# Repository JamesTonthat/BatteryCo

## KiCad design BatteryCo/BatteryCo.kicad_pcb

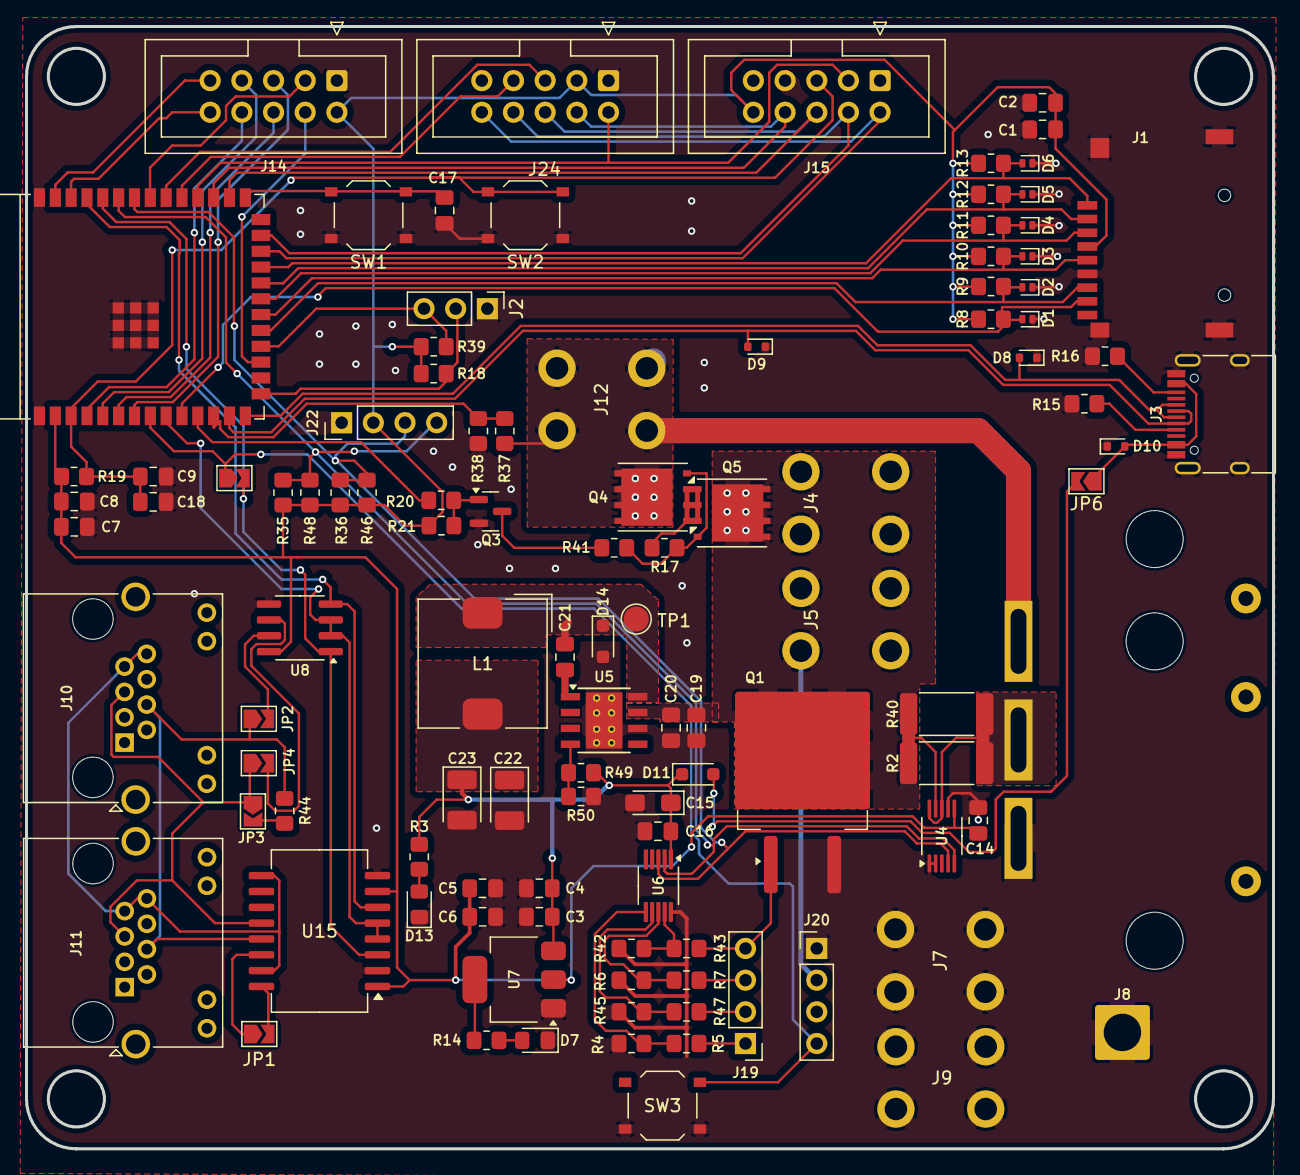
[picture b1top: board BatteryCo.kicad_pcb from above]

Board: 2 copper layers, 100.0 x 90.0 mm, 108 parts (0 on the bottom side), 70 nets.

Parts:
C1, C3, C6, C7, C19, C20: 10uF/25V(20%); C_0805_2012Metric_Pad1.18x1.45mm_HandSolder
C2, C4, C5, C8, C14, C16, C17, C18: 0.1uF/50V(10%); C_0805_2012Metric_Pad1.18x1.45mm_HandSolder
C9: 1uF/16V(10%); C_0805_2012Metric_Pad1.18x1.45mm_HandSolder
C15: 10uF/25V(20%); CP_EIA-3216-18_Kemet-A_Pad1.58x1.35mm_HandSolder
C21: 10nF/50V(10%); C_0805_2012Metric_Pad1.18x1.45mm_HandSolder
C22, C23: 33uF/10V(10%); CP_EIA-3528-21_Kemet-B_Pad1.50x2.35mm_HandSolder
D1, D2, D3, D4, D5, D6: LESD8D3.3CAT5G; D_SOD-882D
D7, D13: LED; LED_0805_2012Metric_Pad1.15x1.40mm_HandSolder
D8, D9, D10: LESD5D5.0CT1G; D_SOD-523
D11, D14: 1N5819WS; D_SOD-323_HandSoldering
J1: Micro_SD_Card_Det2; Hanbo TF-012D
J2: Conn_01x03; PinHeader_1x03_P2.54mm_Vertical
J3: USB_C_Receptacle_USB2.0_16P; USB_C_Receptacle_HRO_TYPE-C-31-M-12
J4, J5, J7, J9, J12: Conn_01x01; T44001
J8: Conn_01x01; SolderWire-2.5sqmm_1x01_D2.4mm_OD4.4mm
J10, J11: RJ45_LED_Shielded; RJ45_Amphenol_RJHSE538X
J14: Conn_02x05_Counter_Clockwise; IDC-Header_2x05_P2.54mm_Vertical
J15, J24: Conn_02x05_Odd_Even; IDC-Header_2x05_P2.54mm_Vertical
J16: Conn_01x03; 45A-ANGLE-PAIR
J19, J20: Conn_01x04; PinHeader_1x04_P2.54mm_Vertical
J22: I2C_BUS0; PinHeader_1x04_P2.54mm_Vertical
JP1, JP2, JP3, JP4, JP5, JP6: SolderJumper_2_Open; SolderJumper-2_P1.3mm_Open_TrianglePad1.0x1.5mm
L1: SLF10145T-101M1R0-PF; L_TDK_SLF10145
Q1: IRLZ44SPbF; TO-263-2
Q3: AO3400A; SOT-23
Q4, Q5: AON6411; AO_DFN-8-1EP_5.55x5.2mm_P1.27mm_EP4.12x4.6mm
R2, R40: 5m; R_2512_6332Metric_Pad1.40x3.35mm_HandSolder
R3: 47K (1%); R_0805_2012Metric_Pad1.20x1.40mm_HandSolder
R4, R6, R8, R9, R10, R11, R12, R13, R17, R18, R19, R21, R37, R39, R42, R45, R49: 10K (1%); R_0805_2012Metric_Pad1.20x1.40mm_HandSolder
R5, R7, R43, R47: 330 (1%); R_0805_2012Metric_Pad1.20x1.40mm_HandSolder
R14, R41: 5.1K (1%); R_0805_2012Metric_Pad1.20x1.40mm_HandSolder
R15, R16, R35, R36, R46, R48: 4.7K (1%); R_0805_2012Metric_Pad1.20x1.40mm_HandSolder
R20: 100 (1%); R_0805_2012Metric_Pad1.20x1.40mm_HandSolder
R38: 1.5k (1%); R_0805_2012Metric_Pad1.20x1.40mm_HandSolder
R44: 120 (1%); R_0805_2012Metric_Pad1.20x1.40mm_HandSolder
R50: 3.3K (1%); R_0805_2012Metric_Pad1.20x1.40mm_HandSolder
SW1, SW2, SW3: SW_Push; SW_Push_1P1T_XKB_TS-1187A
TP1: TestPoint; TestPoint_Pad_D2.0mm
U1: ESP32-S3-WROOM-1
U4: INA228; VSSOP-10_3x3mm_P0.5mm
U5: TPS5430DDA; TI_SO-PowerPAD-8_ThermalVias
U6: MCP4728; MSOP-10_3x3mm_P0.5mm
U7: AMS1117-3.3; SOT-223-3_TabPin2
U8: SP3485EN; SOIC-8_3.9x4.9mm_P1.27mm
U15: CA-IS13092VW; SOIC-16W_7.5x12.8mm_P1.27mm

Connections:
+5V: C3.1, C4.1, C15.1, C16.1, C22.1, C23.1, D11.1 (K), L1.2, R3.1, R49.1, U6.1 (VDD), U7.3 (VI)
BIT_0: J14.10, U1.38 (GPIO2/TOUCH2/ADC1_CH1)
BIT_1: J14.9, U1.39 (GPIO1/TOUCH1/ADC1_CH0)
BIT_2: J14.8, U1.4 (GPIO4/TOUCH4/ADC1_CH3)
BIT_3: J14.7, U1.5 (GPIO5/TOUCH5/ADC1_CH4)
BIT_4: J14.6, U1.6 (GPIO6/TOUCH6/ADC1_CH5)
BIT_5: J14.5, U1.7 (GPIO7/TOUCH7/ADC1_CH6)
BIT_6: J14.4, U1.17 (GPIO9/TOUCH9/ADC1_CH8/FSPIHD/SUBSPIHD)
CHARGER_OFF: R20.2, U1.11 (GPIO18/U1RXD/ADC2_CH7/CLK_OUT3)
CHIP_PU: C9.1, C18.2, J15.5, R19.1, SW2.1, U1.3 (EN)
D1: C21.2, D14.1 (K), L1.1, TP1.1, U5.8 (PH)
ESP_3V3: C1.1, C2.1, C5.1, C6.1, C7.1, C8.1, C14.1, J1.4 (VDD), J14.2, J15.10, J22.2, J24.3, R8.2, R9.2, R10.2, R11.2, R12.2, R13.2, R14.1, R18.1, R19.2, R21.1, R35.1, R36.1, R39.1, R46.1, R48.1, U1.2 (3V3), U4.6 (VS), U7.2 (VO), U8.8 (VCC), U15.1 (VCC), U15.7 (VCCL)
FAN_PWM: J20.4, JP5.1 (A), SW3.2, U1.8 (GPIO15/U0RTS/ADC2_CH4/XTAL_32K_P)
GND3: J10.7, J10.8, J11.7, J11.8, U15.9 (GNDB), U15.15 (GNDB)
GPIO0: C17.2, SW1.2, U1.27 (GPIO0/BOOT)
GPIO19: D9.2 (A2), J3.A7 (D-), J3.B7 (D-), U1.13 (GPIO19/U1RTS/ADC2_CH8/CLK_OUT2/USB_D-)
GPIO20: D8.2 (A2), J3.A6 (D+), J3.B6 (D+), U1.14 (GPIO20/U1CTS/ADC2_CH9/CLK_OUT1/USB_D+)
LCD_SCL: J24.5, U1.32 (MTCK/GPIO39/CLK_OUT3/SUBSPICS1)
LCD_SDA: J24.7, U1.31 (GPIO38/FSPIWP/SUBSPIWP)
LED_ON: J14.3, U1.33 (MTDO/GPIO40/CLK_OUT2)
unnamed: D7.2 (A), R14.2
unnamed: D11.2 (A), JP6.2 (B)
unnamed: D13.2 (A), R3.2
unnamed: J3.A5 (CC1), R15.2
unnamed: J3.B5 (CC2), R16.2
unnamed: JP1.1 (A), U15.14 (VISOIN)
unnamed: JP1.2 (B), U15.16 (VISOOUT)
unnamed: J10.4, J11.4, JP2.1 (A), R44.1, U15.13 (B)
unnamed: JP2.2 (B), U8.7 (B)
unnamed: J10.5, J11.5, JP3.1 (A), JP4.1 (A), U15.12 (A)
unnamed: JP3.2 (B), R44.2
unnamed: JP4.2 (B), U8.6 (A)
unnamed: Q3.3 (D), R41.2
unnamed: Q3.1 (G), R20.1, R21.2
unnamed: Q4.4 (G), Q5.4 (G), R17.2, R41.1
unnamed: Q4.1 (S), Q4.2 (S), Q4.3 (S), Q5.1 (S), Q5.2 (S), Q5.3 (S), R17.1
unnamed: C21.1, U5.1 (BOOT)
unnamed: R49.2, R50.1, U5.4 (VSENSE)
PHOTO_1: J2.2, R18.2, U1.15 (GPIO3/TOUCH3/ADC1_CH2)
PHOTO_2: J2.3, R39.2, U1.18 (GPIO10/TOUCH10/ADC1_CH9/FSPICS0/FSPIIO4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)
RE: U1.9 (GPIO16/U0CTS/ADC2_CH5/XTAL_32K_N), U8.2 (~RE), U8.3 (DE), U15.4 (~RE), U15.5 (DE)
SCL: J22.4, R35.2, R48.2, U1.35 (MTMS/GPIO42), U4.5 (SCL), U6.2 (SCL)
SDA: J22.3, R36.2, R46.2, U1.34 (MTDI/GPIO41/CLK_OUT1), U4.4 (SDA), U6.3 (SDA)
SD_CLK: D3.2 (A2), J1.5 (CLK), R10.1, U1.20 (GPIO12/TOUCH12/ADC2_CH1/FSPICLK/FSPIIO6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)
SD_CMD: D4.2 (A2), J1.3 (CMD), R11.1, U1.21 (GPIO13/TOUCH13/ADC2_CH2/FSPIQ/FSPIIO7/S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)
SD_DATA0: D2.2 (A2), J1.7 (DAT0), R9.1, U1.19 (GPIO11/TOUCH11/ADC2_CH0/FSPID/FSPIIO5/S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)
SD_DATA1: D1.2 (A2), J1.8 (DAT1), R8.1, U1.10 (GPIO17/U1TXD/ADC2_CH6)
SD_DATA2: D6.2 (A2), J1.1 (DAT2), R13.1, U1.23 (GPIO21)
SD_DATA3: D5.2 (A2), J1.2 (DAT3/CD), R12.1, U1.22 (GPIO14/TOUCH14/ADC2_CH3/FSPIWP/FSPIDQS/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)
U0RXD: JP5.2 (B), U1.36 (U0RXD/GPIO44/CLK_OUT2), U8.1 (RO), U15.3 (RO)
U0TXD: U1.37 (U0TXD/GPIO43/CLK_OUT1), U8.4 (DI), U15.6 (DI)
VBUSB: D10.2 (A2), J3.A4 (VBUS), J3.A9 (VBUS), J3.B4 (VBUS), J3.B9 (VBUS), JP6.1 (A)
V_BATT+: J16.2, R2.2, R40.2, U4.8 (Vbus), U4.10 (Vin+)
V_BATT-: C1.2, C2.2, C3.2, C4.2, C5.2, C6.2, C7.2, C8.2, C9.2, C14.2, C15.2, C16.2, C17.1, C18.1, C19.2, C20.2, C22.2, C23.2, D1.1 (A1), D2.1 (A1), D3.1 (A1), D4.1 (A1), D5.1 (A1), D6.1 (A1), D7.1 (K), D8.1 (A1), D9.1 (A1), D10.1 (A1), D13.1 (K), D14.2 (A), J1.6 (VSS), J1.10 (SHIELD), J2.1, J3.A1 (GND), J3.A12 (GND), J3.B1 (GND), J3.B12 (GND), J3.S1 (SHIELD), J7.1, J8.1, J9.1, J14.1, J15.7, J16.3, J20.1, J22.1, J24.1, Q1.3 (S), Q3.2 (S), R4.2, R6.2, R15.1, R16.1, R38.2, R42.2, R45.2, R50.2, SW1.1, SW2.2, SW3.1, U1.1 (GND), U1.40 (GND), U1.41 (GND), U4.1 (A1), U4.2 (A0), U4.7 (GND), U5.6 (GND), U5.9 (GNDPAD), U6.10 (VSS), U7.1 (GND), U8.5 (GND), U15.2 (GNDA), U15.8 (GNDA)
V_CHA: R4.1, R5.1, U6.6 (VOUTA)
V_CHARGER+: J12.1, J16.1, Q4.5 (D), R37.1
V_CHARGER_REF: R37.2, R38.1, U1.12 (GPIO8/TOUCH8/ADC1_CH7/SUBSPICS1)
V_CHA_OUT: J19.1, R5.2
V_CHB: R45.1, R47.1, U6.7 (VOUTB)
V_CHB_OUT: J19.2, R47.2
V_CHC: R6.1, R7.1, U6.8 (VOUTC)
V_CHC_OUT: J19.3, R7.2
V_CHD: R42.1, R43.1, U6.9 (VOUTD)
V_CHD_OUT: J19.4, Q1.1 (G), R43.2
V_LOAD+: C19.1, C20.1, J4.1, J5.1, J20.2, Q1.2 (D), Q5.5 (D), R2.1, R40.1, U4.9 (Vin-), U5.7 (VIN)
W_INT: J15.3, J24.2, U1.30 (SPIDQS/GPIO37/FSPIQ/SUBSPIQ)
W_MISO: J15.8, J24.4, U1.29 (SPIIO7/GPIO36/FSPICLK/SUBSPICLK)
W_MOSI: J15.6, J24.6, U1.28 (SPIIO6/GPIO35/FSPID/SUBSPID)
W_SCLK: J15.2, J24.10, U1.24 (GPIO47/SPICLK_P/SUBSPICLK_P_DIFF)
W_SCS: J15.4, J24.8, U1.25 (GPIO48/SPICLK_N/SUBSPICLK_N_DIFF)

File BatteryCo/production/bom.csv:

Designator,Footprint,Quantity,Value,LCSC Part #
"C1, C12, C13, C3, C6, C7",0805,6,10uF/25V(20%),C15850
"C10, C11, C14, C16, C17, C18, C2, C4, C5, C8",0805,10,0.1uF/50V(10%),C49678
C15,CP_EIA-3216-18_Kemet-A_Pad1.58x1.35mm_HandSolder,1,10uF/25V(20%),C7171
C9,0805,1,1uF/16V(10%),C28323
"D1, D2, D3, D4, D5, D6",D_SOD-882D,6,LESD8D3.3CAT5G,C5199186
"D10, D8, D9",D_SOD-523,3,LESD5D5.0CT1G,C383211
D11,D_SOD-323,1,1N5819WS,C191023
D13,0805,1,LED,C2297
D7,0805,1,LED,C84256
J1,Hanbo TF-012D,1,Micro_SD_Card_Det2,C2874207
"J12, J13, J16, J17, J18, J4, J5, J6, J7, J8, J9",SolderWire-2.5sqmm_1x01_D2.4mm_OD4.4mm,11,Conn_01x01,
J3,USB_C_Receptacle_HRO_TYPE-C-31-M-12,1,USB_C_Receptacle_USB2.0_16P, C165948
Q3,SOT-23,1,AO3400A,C20917
"Q4, Q5",AO_DFN-8-1EP_5.55x5.2mm_P1.27mm_EP4.12x4.6mm,2,AON6411,C81007
"R10, R11, R12, R13, R17, R18, R19, R21, R37, R39, R42, R45, R5, R6, R8, R9",0805,16,10K (1%),C17414
"R14, R41",0805,2,5.1K (1%),C27834
"R15, R16, R35, R36",0805,4,4.7K (1%),C17673
"R2, R40",2512,2,5m,C3152738
"R20, R3",0805,2,100 (1%), C17408
R38,0805,1,1.5k (1%), C4310
"R4, R43, R47, R7",0805,4,330 (1%),C17630
R44,0805,1,120 (1%),C17437
"SW1, SW2, SW3",SW_Push_1P1T_XKB_TS-1187A,3,SW_Push,C318884
U4,VSSOP-10_3x3mm_P0.5mm,1,INA228,C2887910
U6,MSOP-10_3x3mm_P0.5mm,1,MCP4728,C108207
U7,SOT-223-3_TabPin2,1,AMS1117-3.3,C6186
U8,SOIC-8_3.9x4.9mm_P1.27mm,1,SP3485EN,C8963
U9,TO-252-2,1,L78M05ABDT-TR,C58069

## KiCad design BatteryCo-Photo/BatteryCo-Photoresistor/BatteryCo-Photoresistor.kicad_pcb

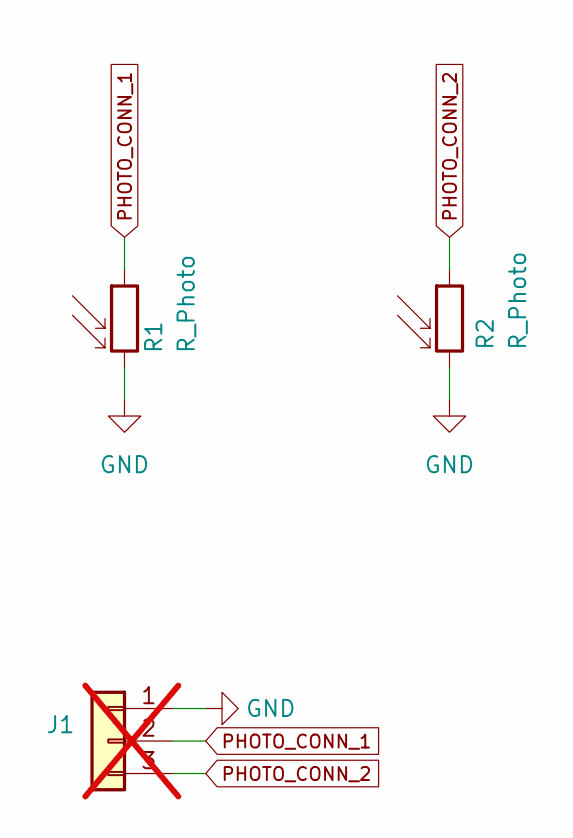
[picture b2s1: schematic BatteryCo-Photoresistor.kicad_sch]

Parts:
J1: Conn_01x03; PinHeader_1x03_P2.54mm_Vertical; not fitted
R1, R2: R_Photo; R_LDR_5.1x4.3mm_P3.4mm_Vertical

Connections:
GND: J1.1, R1.2, R2.2
PHOTO_CONN_1: J1.2, R1.1
PHOTO_CONN_2: J1.3, R2.1

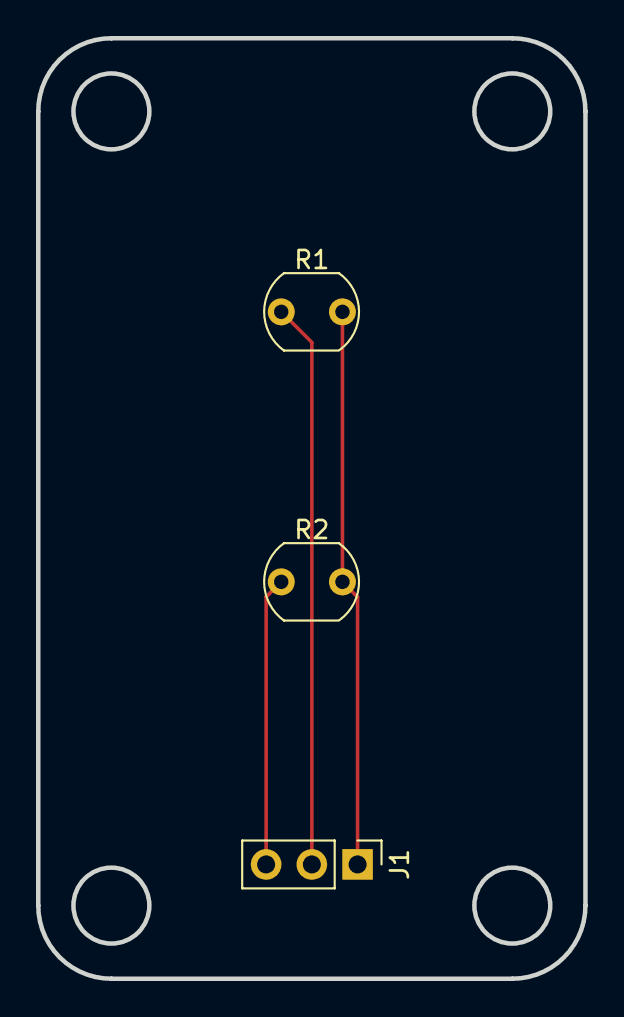
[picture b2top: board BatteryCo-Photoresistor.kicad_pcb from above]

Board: 2 copper layers, 30.4 x 52.2 mm, 3 parts (0 on the bottom side), 3 nets.

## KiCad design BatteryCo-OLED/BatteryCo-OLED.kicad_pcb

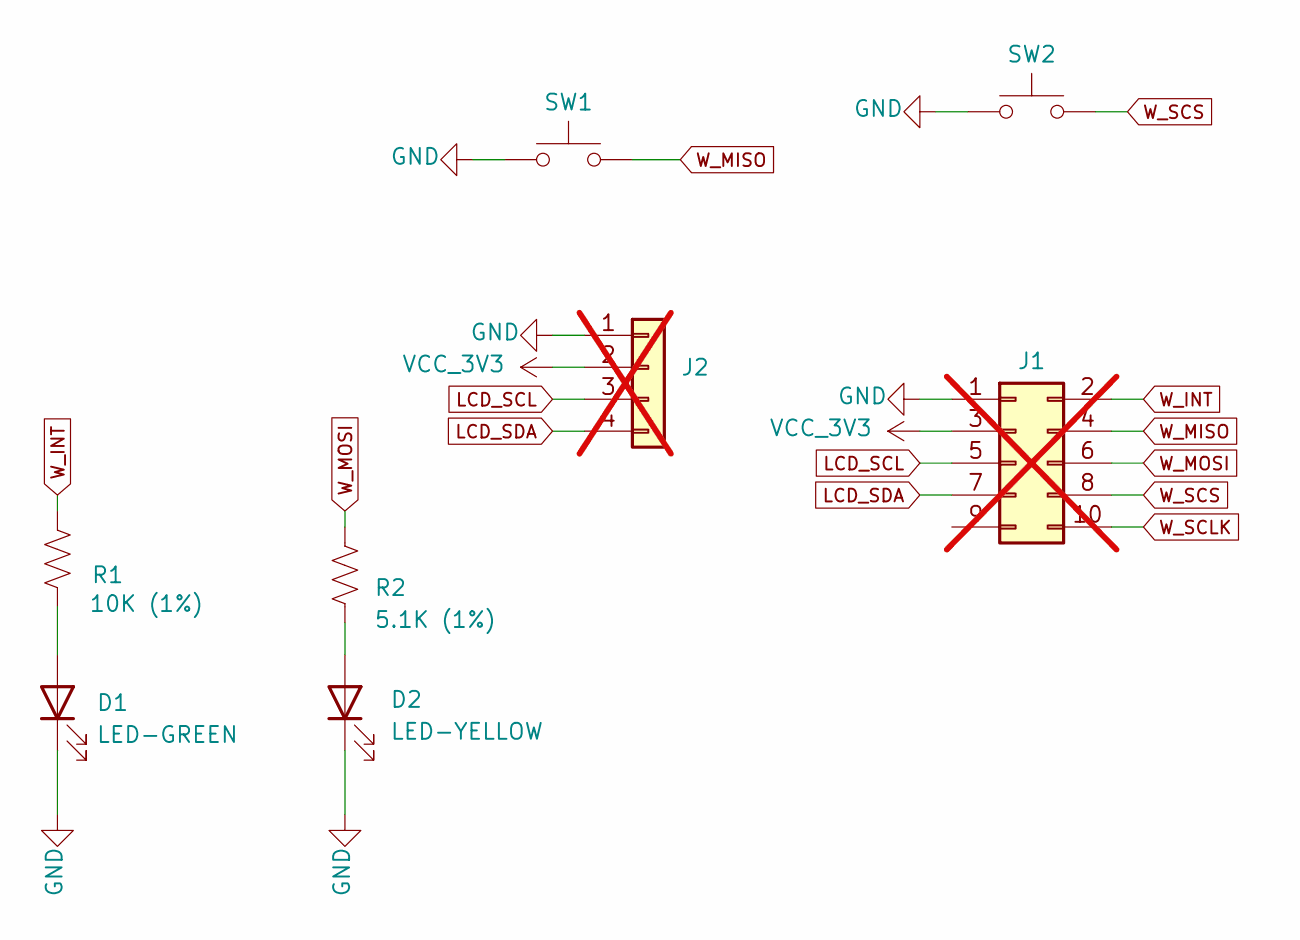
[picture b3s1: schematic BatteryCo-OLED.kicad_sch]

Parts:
D1: LED-GREEN; LED_0805_2012Metric_Pad1.15x1.40mm_HandSolder; LCSC Part # C2297
D2: LED-YELLOW; LED_0805_2012Metric_Pad1.15x1.40mm_HandSolder; LCSC Part # C2296
J1: Conn_02x05_Odd_Even; IDC-Header_2x05_P2.54mm_Vertical; not fitted
J2: Conn_01x04; PinHeader_1x04_P2.54mm_Vertical; not fitted
R1: 10K (1%); R_0805_2012Metric_Pad1.20x1.40mm_HandSolder; LCSC Part # C17414
R2: 5.1K (1%); R_0805_2012Metric_Pad1.20x1.40mm_HandSolder; LCSC Part # C27834
SW1, SW2: SW_Push; SW_Push_1P1T_XKB_TS-1187A; LCSC Part # C318884

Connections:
GND: D1.1 (K), D2.1 (K), J1.1, J2.1, SW1.1, SW2.1
LCD_SCL: J1.5, J2.3
LCD_SDA: J1.7, J2.4
unnamed: D1.2 (A), R1.2
unnamed: D2.2 (A), R2.1
VCC_3V3: J1.3, J2.2
W_INT: J1.2, R1.1
W_MISO: J1.4, SW1.2
W_MOSI: J1.6, R2.2
W_SCLK: J1.10
W_SCS: J1.8, SW2.2

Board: 2 copper layers, 8 parts (1 on the bottom side), 10 nets, no tracks yet.

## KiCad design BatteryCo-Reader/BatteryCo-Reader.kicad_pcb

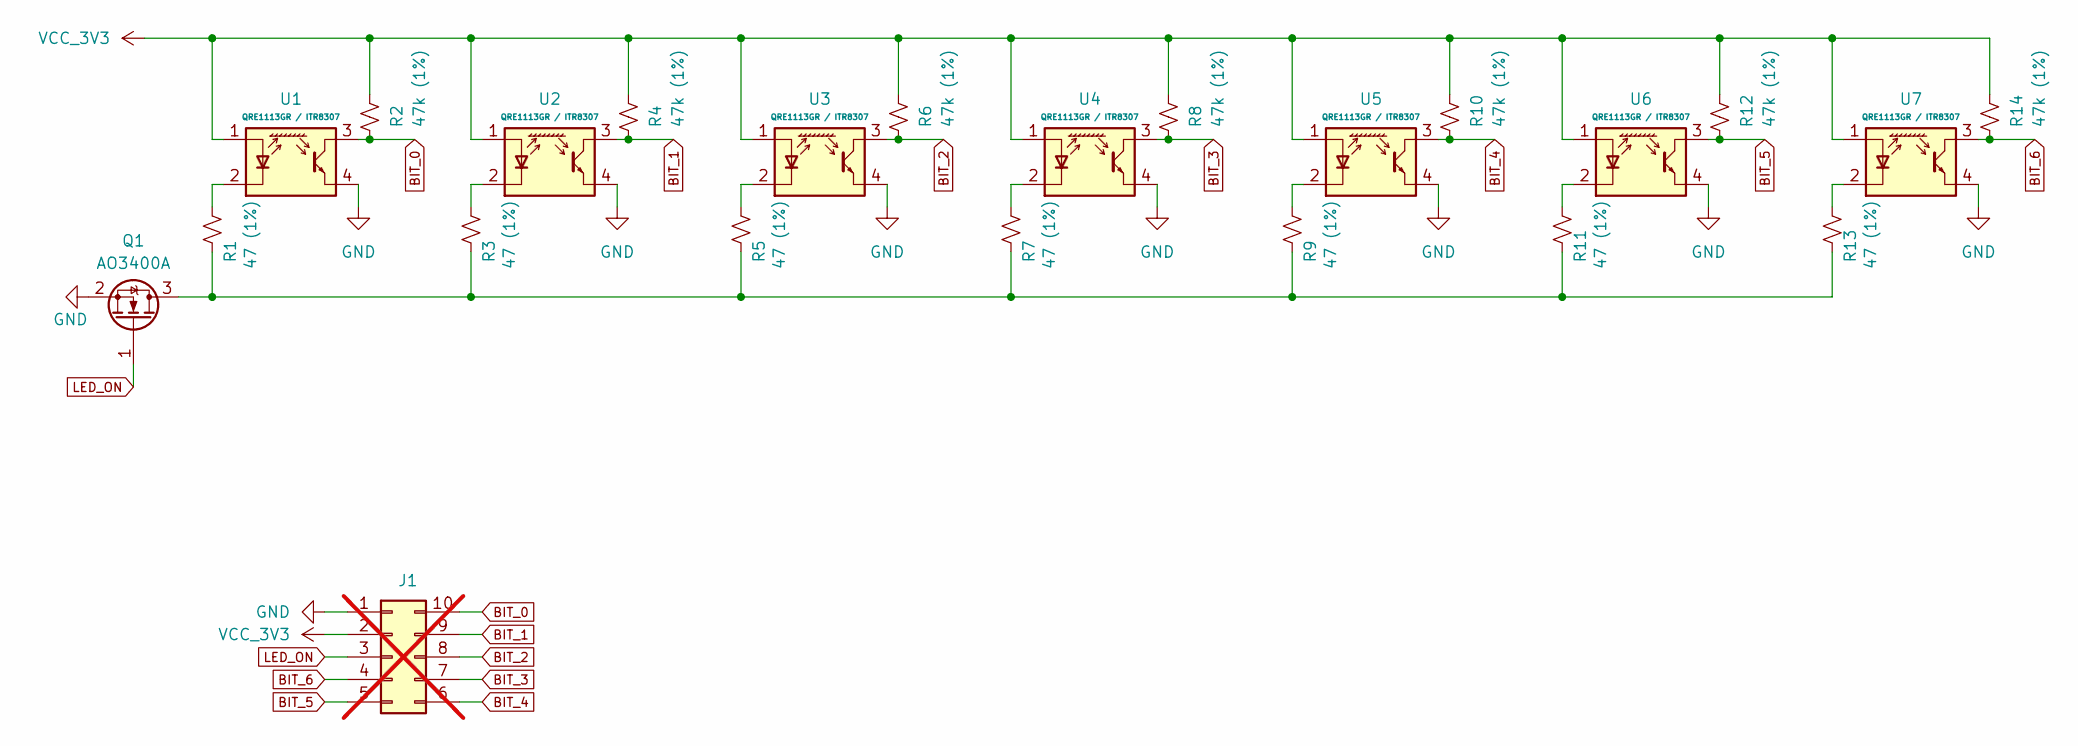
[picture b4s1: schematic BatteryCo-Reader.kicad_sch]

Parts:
J1: Conn_02x05_Counter_Clockwise; IDC-Header_2x05_P2.54mm_Vertical; not fitted
Q1: AO3400A; SOT-23; LCSC Part # C20917
R1, R3, R5, R7, R9, R11, R13: 47 (1%); R_0805_2012Metric_Pad1.20x1.40mm_HandSolder; LCSC Part # C17714
R2, R4, R6, R8, R10, R12, R14: 47k (1%); R_0805_2012Metric_Pad1.20x1.40mm_HandSolder; LCSC Part # C17713
U1, U2, U3, U4, U5, U6, U7: QRE1113GR / ITR8307; OnSemi_CASE100CY; LCSC Part # C81632

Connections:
BIT_0: J1.10, R2.2, U1.3
BIT_1: J1.9, R4.2, U2.3
BIT_2: J1.8, R6.2, U3.3
BIT_3: J1.7, R8.2, U4.3
BIT_4: J1.6, R10.2, U5.3
BIT_5: J1.5, R12.2, U6.3
BIT_6: J1.4, R14.2, U7.3
GND: J1.1, Q1.2 (S), U1.4, U2.4, U3.4, U4.4, U5.4, U6.4, U7.4
LED_ON: J1.3, Q1.1 (G)
unnamed: Q1.3 (D), R1.2, R3.2, R5.2, R7.2, R9.2, R11.2, R13.2
unnamed: R1.1, U1.2 (K)
unnamed: R3.1, U2.2 (K)
unnamed: R5.1, U3.2 (K)
unnamed: R7.1, U4.2 (K)
unnamed: R9.1, U5.2 (K)
unnamed: R11.1, U6.2 (K)
unnamed: R13.1, U7.2 (K)
VCC_3V3: J1.2, R2.1, R4.1, R6.1, R8.1, R10.1, R12.1, R14.1, U1.1 (A), U2.1 (A), U3.1 (A), U4.1 (A), U5.1 (A), U6.1 (A), U7.1 (A)

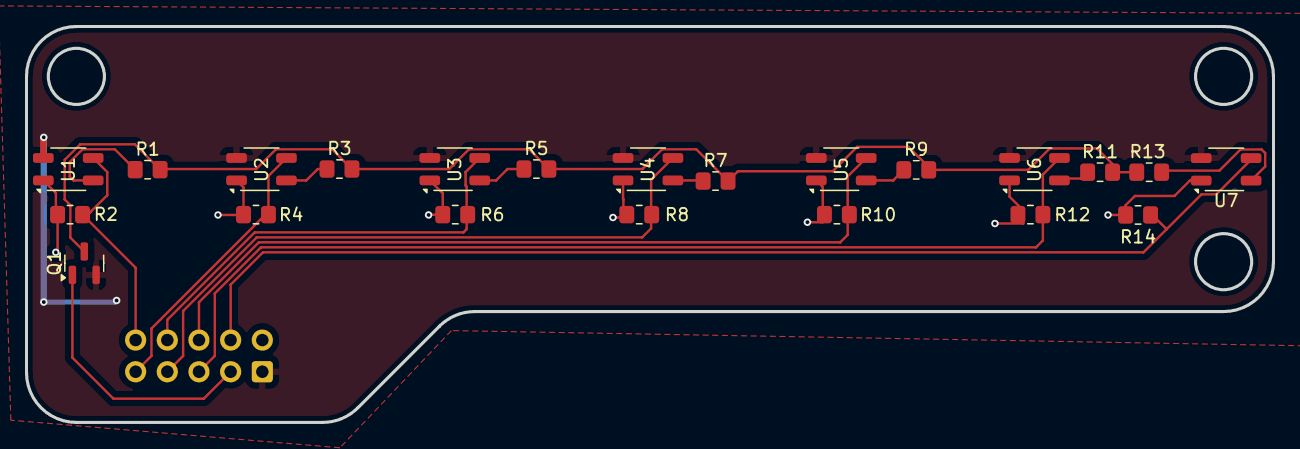
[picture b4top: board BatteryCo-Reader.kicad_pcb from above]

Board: 2 copper layers, 100.0 x 31.8 mm, 23 parts (1 on the bottom side), 18 nets.

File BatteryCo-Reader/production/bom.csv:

Designator,Footprint,Quantity,Value,LCSC Part #
J1,IDC-Header_2x05_P2.54mm_Vertical,1,Conn_02x05_Counter_Clockwise,
Q1,SOT-23,1,AO3400A,C20917
"R1, R11, R13, R3, R5, R7, R9",0805,7,47 (1%), C17714
"R10, R12, R14, R2, R4, R6, R8",0805,7,47k (1%),C17713
"U1, U2, U3, U4, U5, U6, U7",OnSemi_CASE100CY,7,QRE1113GR / ITR8307,C81632

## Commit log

2025-10-04 Commit before changing to isolated measurement
2025-10-04 no message
